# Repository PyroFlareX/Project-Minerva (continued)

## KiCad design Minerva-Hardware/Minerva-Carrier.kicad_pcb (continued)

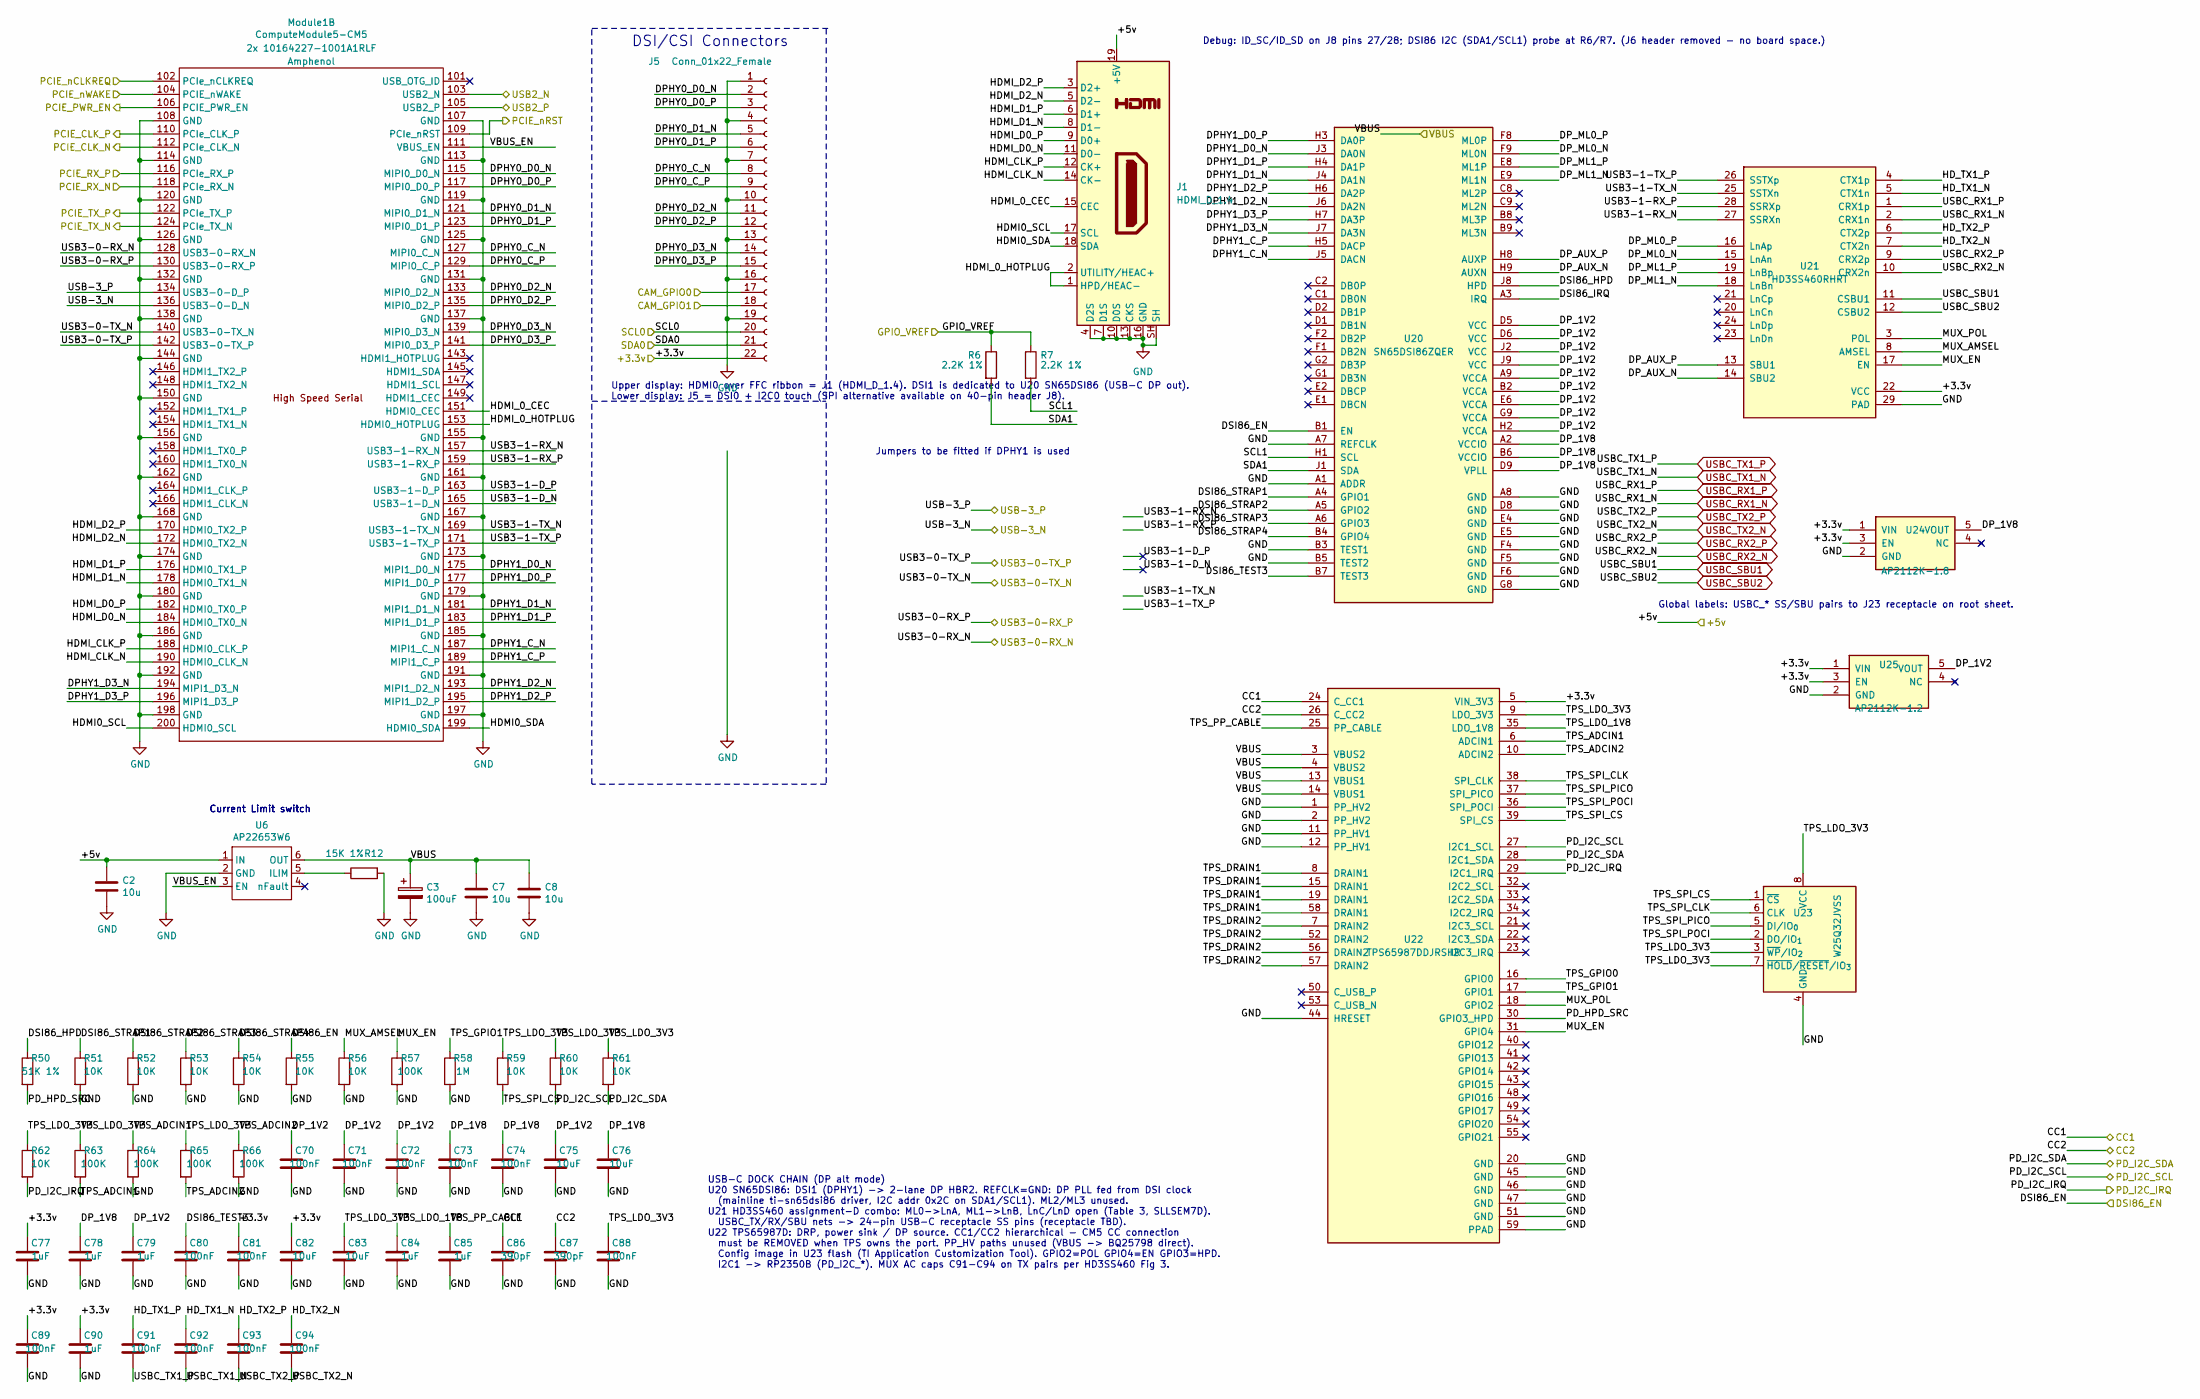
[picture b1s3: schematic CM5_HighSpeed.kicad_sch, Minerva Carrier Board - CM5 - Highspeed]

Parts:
C2, C7, C8: 10u; C_0805_2012Metric; Part Description 10uF 10% 10V Ceramic Capacitor X7R 0805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
C3: 100uF; CP_EIA-7343-31_Kemet-D; Part Description Capacitor, SP-Cap, 100u, 6.3V, 15mR ESR
C70, C71, C72, C73, C74, C80, C81, C88, C89, C91, C92, C93, C94: 100nF; C_0402_1005Metric; MPN EMK105B7104KV-F
C75, C76, C82, C83: 10uF; C_0603_1608Metric; MPN CL10A106KP8NNNC
C77, C78, C79, C84, C85, C90: 1uF; C_0402_1005Metric; MPN CC0402KRX5R6BB105
C86, C87: 390pF; C_0402_1005Metric; MPN GRM1555C1H391JA01D
J1: HDMI_D_1.4; TE_2-1734839-0_1x20-1MP_P0.5mm_Horizontal; MPN 2-1734839-0
J5: Conn_01x22_Female; Hirose_FH12-22S-0.5SH_1x22-1MP_P0.50mm_Horizontal; Part Description 22 Position FFC, FPC Connector Contacts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
Module1: ComputeModule5-CM5; Raspberry-Pi-5-Compute-Module; Part Description 100 Position Connector Receptacle, Cent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
R6, R7: 2.2K 1%; R_0402_1005Metric; Part Description Resistor 2.2K M1005 1% 63mW
R12: 15K 1%; R_0402_1005Metric; Part Description Resistor 15K M1005 1% 63mW
R50: 51K 1%; R_0402_1005Metric; MPN RC0402FR-0751KL
R51, R52, R53, R54, R55, R56, R59, R60, R61, R62: 10K; R_0402_1005Metric; MPN RC0402FR-0710KL
R57, R63, R64, R65, R66: 100K; R_0402_1005Metric; MPN RC0402FR-07100KL
R58: 1M; R_0402_1005Metric; MPN RC0402FR-071ML
U6: AP22653W6; SOT-23-6; Part Description Power Switch/Driver 1:1 P-Channel 2.1A 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
U20: SN65DSI86ZQER; nFBGA-64_ZQE_5x5mm_P0.5mm; Part Description MIPI DSI to DP1.2 bridge, LCSC C575556
U21: HD3SS460RHRT; WQFN-28-1EP_3.5x5.5mm_P0.5mm_EP2.05x4.05mm_ThermalVias; Part Description USB3/DP alt-mode passive mux, LCSC C215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
U22: TPS65987DDJRSHR; TPS65987D_VQFN56_RSH; Part Description USB-C PD3.0 controller w/ DP alt mode, 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
U23: W25Q32JVSS; SOIC-8_5.3x5.3mm_P1.27mm; Part Description TPS65987D config flash (any 2Mbit+ SPI 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
U24: AP2112K-1.8; SOT-23-5; Part Description 1.8V LDO for SN65DSI86 VCCIO/VPLL
U25: AP2112K-1.2; SOT-23-5; Part Description 1.2V LDO for SN65DSI86 VCC/VCCA

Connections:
+3.3v: C77.1, C81.1, C82.1, C89.1, C90.1, J5.22, U21.22 (VCC), U22.5 (VIN_3V3), U24.1 (VIN), U24.3 (EN), U25.1 (VIN), U25.3 (EN); also elsewhere on the board
/+5v: C2.1, J1.19 (+5V), U6.1 (IN); also elsewhere on the board
/CC1: C86.1, U22.24 (C_CC1); also elsewhere on the board
/CC2: C87.1, U22.26 (C_CC2); also elsewhere on the board
/CM5_GPIO/CAM_GPIO0: J5.17; also elsewhere on the board
/CM5_GPIO/CAM_GPIO1: J5.18; also elsewhere on the board
/CM5_GPIO/GPIO_VREF: R6.1, R7.1; also elsewhere on the board
/CM5_HighSpeed/DPHY0_C_N: J5.8, Module1.127 (MIPI0_C_N)
/CM5_HighSpeed/DPHY0_C_P: J5.9, Module1.129 (MIPI0_C_P)
/CM5_HighSpeed/DPHY0_D0_N: J5.2, Module1.115 (MIPI0_D0_N)
/CM5_HighSpeed/DPHY0_D0_P: J5.3, Module1.117 (MIPI0_D0_P)
/CM5_HighSpeed/DPHY0_D1_N: J5.5, Module1.121 (MIPI0_D1_N)
/CM5_HighSpeed/DPHY0_D1_P: J5.6, Module1.123 (MIPI0_D1_P)
/CM5_HighSpeed/DPHY0_D2_N: J5.11, Module1.133 (MIPI0_D2_N)
/CM5_HighSpeed/DPHY0_D2_P: J5.12, Module1.135 (MIPI0_D2_P)
/CM5_HighSpeed/DPHY0_D3_N: J5.14, Module1.139 (MIPI0_D3_N)
/CM5_HighSpeed/DPHY0_D3_P: J5.15, Module1.141 (MIPI0_D3_P)
/CM5_HighSpeed/DPHY1_C_N: Module1.187 (MIPI1_C_N), U20.J5 (DACN)
/CM5_HighSpeed/DPHY1_C_P: Module1.189 (MIPI1_C_P), U20.H5 (DACP)
/CM5_HighSpeed/DPHY1_D0_N: Module1.175 (MIPI1_D0_N), U20.J3 (DA0N)
/CM5_HighSpeed/DPHY1_D0_P: Module1.177 (MIPI1_D0_P), U20.H3 (DA0P)
/CM5_HighSpeed/DPHY1_D1_N: Module1.181 (MIPI1_D1_N), U20.J4 (DA1N)
/CM5_HighSpeed/DPHY1_D1_P: Module1.183 (MIPI1_D1_P), U20.H4 (DA1P)
/CM5_HighSpeed/DPHY1_D2_N: Module1.193 (MIPI1_D2_N), U20.J6 (DA2N)
/CM5_HighSpeed/DPHY1_D2_P: Module1.195 (MIPI1_D2_P), U20.H6 (DA2P)
/CM5_HighSpeed/DPHY1_D3_N: Module1.194 (MIPI1_D3_N), U20.J7 (DA3N)
/CM5_HighSpeed/DPHY1_D3_P: Module1.196 (MIPI1_D3_P), U20.H7 (DA3P)
/CM5_HighSpeed/DP_1V2: C70.1, C71.1, C72.1, C75.1, C79.1, U20.A9 (VCCA), U20.B2 (VCCA), U20.D5 (VCC), U20.D6 (VCC), U20.E6 (VCCA), U20.G9 (VCCA), U20.H2 (VCCA), U20.J2 (VCC), U20.J9 (VCC), U25.5 (VOUT)
/CM5_HighSpeed/DP_1V8: C73.1, C74.1, C76.1, C78.1, U20.A2 (VCCIO), U20.B6 (VCCIO), U20.D9 (VPLL), U24.5 (VOUT)
/CM5_HighSpeed/DP_AUX_N: U20.H9 (AUXN), U21.14 (SBU2)
/CM5_HighSpeed/DP_AUX_P: U20.H8 (AUXP), U21.13 (SBU1)
/CM5_HighSpeed/DP_ML0_N: U20.F9 (ML0N), U21.15 (LnAn)
/CM5_HighSpeed/DP_ML0_P: U20.F8 (ML0P), U21.16 (LnAp)
/CM5_HighSpeed/DP_ML1_N: U20.E9 (ML1N), U21.18 (LnBn)
/CM5_HighSpeed/DP_ML1_P: U20.E8 (ML1P), U21.19 (LnBp)
/CM5_HighSpeed/DSI86_HPD: R50.1, U20.J8 (HPD)
/CM5_HighSpeed/DSI86_IRQ: U20.A3 (IRQ)
/CM5_HighSpeed/DSI86_STRAP1: R51.1, U20.A4 (GPIO1)
/CM5_HighSpeed/DSI86_STRAP2: R52.1, U20.A5 (GPIO2)
/CM5_HighSpeed/DSI86_STRAP3: R53.1, U20.A6 (GPIO3)
/CM5_HighSpeed/DSI86_STRAP4: R54.1, U20.B4 (GPIO4)
/CM5_HighSpeed/DSI86_TEST3: C80.1, U20.B7 (TEST3)
/CM5_HighSpeed/HDMI0_SCL: J1.17 (SCL), Module1.200 (HDMI0_SCL)
/CM5_HighSpeed/HDMI0_SDA: J1.18 (SDA), Module1.199 (HDMI0_SDA)
/CM5_HighSpeed/HDMI_0_CEC: J1.15 (CEC), Module1.151 (HDMI0_CEC)
/CM5_HighSpeed/HDMI_0_HOTPLUG: J1.1 (HPD/HEAC-), J1.2 (UTILITY/HEAC+), Module1.153 (HDMI0_HOTPLUG)
/CM5_HighSpeed/HDMI_CLK_N: J1.14 (CK-), Module1.190 (HDMI0_CLK_N)
/CM5_HighSpeed/HDMI_CLK_P: J1.12 (CK+), Module1.188 (HDMI0_CLK_P)
/CM5_HighSpeed/HDMI_D0_N: J1.11 (D0-), Module1.184 (HDMI0_TX0_N)
/CM5_HighSpeed/HDMI_D0_P: J1.9 (D0+), Module1.182 (HDMI0_TX0_P)
/CM5_HighSpeed/HDMI_D1_N: J1.8 (D1-), Module1.178 (HDMI0_TX1_N)
/CM5_HighSpeed/HDMI_D1_P: J1.6 (D1+), Module1.176 (HDMI0_TX1_P)
/CM5_HighSpeed/HDMI_D2_N: J1.5 (D2-), Module1.172 (HDMI0_TX2_N)
/CM5_HighSpeed/HDMI_D2_P: J1.3 (D2+), Module1.170 (HDMI0_TX2_P)
/CM5_HighSpeed/HD_TX1_N: C92.1, U21.5 (CTX1n)
/CM5_HighSpeed/HD_TX1_P: C91.1, U21.4 (CTX1p)
/CM5_HighSpeed/HD_TX2_N: C94.1, U21.7 (CTX2n)
/CM5_HighSpeed/HD_TX2_P: C93.1, U21.6 (CTX2p)
/CM5_HighSpeed/MUX_AMSEL: R56.1, U21.8 (AMSEL)
/CM5_HighSpeed/MUX_EN: R57.1, U21.17 (EN), U22.31 (GPIO4)
/CM5_HighSpeed/MUX_POL: U21.3 (POL), U22.18 (GPIO2)
/CM5_HighSpeed/PCIE_CLK_N: Module1.112 (PCIe_CLK_N); also elsewhere on the board
/CM5_HighSpeed/PCIE_CLK_P: Module1.110 (PCIe_CLK_P); also elsewhere on the board
/CM5_HighSpeed/PCIE_PWR_EN: Module1.106 (PCIE_PWR_EN); also elsewhere on the board
/CM5_HighSpeed/PCIE_RX_N: Module1.118 (PCIe_RX_N); also elsewhere on the board
/CM5_HighSpeed/PCIE_RX_P: Module1.116 (PCIe_RX_P); also elsewhere on the board
/CM5_HighSpeed/PCIE_TX_N: Module1.124 (PCIe_TX_N); also elsewhere on the board
/CM5_HighSpeed/PCIE_TX_P: Module1.122 (PCIe_TX_P); also elsewhere on the board
/CM5_HighSpeed/PCIE_nCLKREQ: Module1.102 (PCIe_nCLKREQ); also elsewhere on the board
/CM5_HighSpeed/PCIE_nWAKE: Module1.104 (PCIE_nWAKE); also elsewhere on the board
/CM5_HighSpeed/PD_HPD_SRC: R50.2, U22.30 (GPIO3_HPD)
/CM5_HighSpeed/SCL0: J5.20; also elsewhere on the board
/CM5_HighSpeed/SCL1: R7.2, U20.H1 (SCL)
/CM5_HighSpeed/SDA0: J5.21; also elsewhere on the board
/CM5_HighSpeed/SDA1: R6.2, U20.J1 (SDA)
/CM5_HighSpeed/TPS_ADCIN1: R63.2, R64.1, U22.6 (ADCIN1)
/CM5_HighSpeed/TPS_ADCIN2: R65.2, R66.1, U22.10 (ADCIN2)
/CM5_HighSpeed/TPS_DRAIN1: U22.8 (DRAIN1), U22.15 (DRAIN1), U22.19 (DRAIN1), U22.58 (DRAIN1)
/CM5_HighSpeed/TPS_DRAIN2: U22.7 (DRAIN2), U22.52 (DRAIN2), U22.56 (DRAIN2), U22.57 (DRAIN2)
/CM5_HighSpeed/TPS_GPIO0: U22.16 (GPIO0)
/CM5_HighSpeed/TPS_GPIO1: R58.1, U22.17 (GPIO1)
/CM5_HighSpeed/TPS_LDO_1V8: C84.1, U22.35 (LDO_1V8)
/CM5_HighSpeed/TPS_LDO_3V3: C83.1, C88.1, R59.1, R60.1, R61.1, R62.1, R63.1, R65.1, U22.9 (LDO_3V3), U23.3 (~WP/IO_{2}), U23.7 (~HOLD/~RESET/IO_{3}), U23.8 (VCC)
/CM5_HighSpeed/TPS_PP_CABLE: C85.1, U22.25 (PP_CABLE)
/CM5_HighSpeed/TPS_SPI_CLK: U22.38 (SPI_CLK), U23.6 (CLK)
/CM5_HighSpeed/TPS_SPI_CS: R59.2, U22.39 (SPI_CS), U23.1 (~CS)
/CM5_HighSpeed/TPS_SPI_PICO: U22.37 (SPI_PICO), U23.5 (DI/IO_{0})
/CM5_HighSpeed/TPS_SPI_POCI: U22.36 (SPI_POCI), U23.2 (DO/IO_{1})
/CM5_HighSpeed/USB3-0-RX_N: Module1.128 (USB3-0-RX_N); also elsewhere on the board
/CM5_HighSpeed/USB3-0-RX_P: Module1.130 (USB3-0-RX_P); also elsewhere on the board
/CM5_HighSpeed/USB3-0-TX_N: Module1.140 (USB3-0-TX_N); also elsewhere on the board
/CM5_HighSpeed/USB3-0-TX_P: Module1.142 (USB3-0-TX_P); also elsewhere on the board
/CM5_HighSpeed/USB3-1-D_N: Module1.165 (USB3-1-D_N)
/CM5_HighSpeed/USB3-1-D_P: Module1.163 (USB3-1-D_P)
/CM5_HighSpeed/USB3-1-RX_N: Module1.157 (USB3-1-RX_N), U21.27 (SSRXn)
/CM5_HighSpeed/USB3-1-RX_P: Module1.159 (USB3-1-RX_P), U21.28 (SSRXp)
/CM5_HighSpeed/USB3-1-TX_N: Module1.169 (USB3-1-TX_N), U21.25 (SSTXn)
/CM5_HighSpeed/USB3-1-TX_P: Module1.171 (USB3-1-TX_P), U21.26 (SSTXp)
/CM5_HighSpeed/USB-3_N: Module1.136 (USB3-0-D_N); also elsewhere on the board
/CM5_HighSpeed/USB-3_P: Module1.134 (USB3-0-D_P); also elsewhere on the board
/CM5_HighSpeed/VBUS_EN: Module1.111 (VBUS_EN), U6.3 (EN)
/DSI86_EN: R55.1, U20.B1 (EN); also elsewhere on the board
/PCIE_nRST: Module1.109 (PCIe_nRST); also elsewhere on the board
/PD_I2C_IRQ: R62.2, U22.29 (I2C1_IRQ); also elsewhere on the board
/PD_I2C_SCL: R60.2, U22.27 (I2C1_SCL); also elsewhere on the board
/PD_I2C_SDA: R61.2, U22.28 (I2C1_SDA); also elsewhere on the board
/USB2_N: Module1.103 (USB2_N); also elsewhere on the board
/USB2_P: Module1.105 (USB2_P); also elsewhere on the board
/VBUS: C3.1, C7.1, C8.1, U6.6 (OUT), U22.3 (VBUS2), U22.4 (VBUS2), U22.13 (VBUS1), U22.14 (VBUS1); also elsewhere on the board
GND: C2.2, C3.2, C7.2, C8.2, C70.2, C71.2, C72.2, C73.2, C74.2, C75.2, C76.2, C77.2, C78.2, C79.2, C80.2, C81.2, C82.2, C83.2, C84.2, C85.2, C86.2, C87.2, C88.2, C89.2, C90.2, J1.4 (D2S), J1.7 (D1S), J1.10 (D0S), J1.13 (CKS), J1.16 (GND), J1.20, J1.MP, J1.SH, J5.1, J5.4, J5.7, J5.10, J5.13, J5.16, J5.19, Module1.107 (GND), Module1.108 (GND), Module1.113 (GND), Module1.114 (GND), Module1.119 (GND), Module1.120 (GND), Module1.125 (GND), Module1.126 (GND), Module1.131 (GND), Module1.132 (GND), Module1.137 (GND), Module1.138 (GND), Module1.144 (GND), Module1.150 (GND), Module1.155 (GND), Module1.156 (GND), Module1.161 (GND), Module1.162 (GND), Module1.167 (GND), Module1.168 (GND), Module1.173 (GND), Module1.174 (GND), Module1.179 (GND), Module1.180 (GND), Module1.185 (GND), Module1.186 (GND), Module1.191 (GND), Module1.192 (GND), Module1.197 (GND), Module1.198 (GND), R12.2, R51.2, R52.2, R53.2, R54.2, R55.2, R56.2, R57.2, R58.2, R64.2, R66.2, U6.2 (GND), U20.A1 (ADDR), U20.A7 (REFCLK), U20.A8 (GND), U20.B3 (TEST1), U20.B5 (TEST2), U20.D8 (GND), U20.E4 (GND), U20.E5 (GND), U20.F4 (GND), U20.F5 (GND), U20.F6 (GND), U20.G8 (GND), U21.29 (PAD), U22.1 (PP_HV2), U22.2 (PP_HV2), U22.11 (PP_HV1), U22.12 (PP_HV1), U22.20 (GND), U22.44 (HRESET), U22.45 (GND), U22.46 (GND), U22.47 (GND), U22.51 (GND), U22.59 (PPAD), U23.4 (GND), U24.2 (GND), U25.2 (GND); also elsewhere on the board
unnamed: R12.1, U6.5 (ILIM)
USBC_RX1_N: U21.2 (CRX1n); also elsewhere on the board
USBC_RX1_P: U21.1 (CRX1p); also elsewhere on the board
USBC_RX2_N: U21.10 (CRX2n); also elsewhere on the board
USBC_RX2_P: U21.9 (CRX2p); also elsewhere on the board
USBC_SBU1: U21.11 (CSBU1); also elsewhere on the board
USBC_SBU2: U21.12 (CSBU2); also elsewhere on the board
USBC_TX1_N: C92.2; also elsewhere on the board
USBC_TX1_P: C91.2; also elsewhere on the board
USBC_TX2_N: C94.2; also elsewhere on the board
USBC_TX2_P: C93.2; also elsewhere on the board

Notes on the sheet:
Upper display: HDMI0 over FFC ribbon = J1 (HDMI_D_1.4). DSI1 is dedicated to U20 SN65DSI86 (USB-C DP out). Lower display: J5 = DSI0 + I2C0 touch (SPI alternative available on 40-pin header J8).
Jumpers to be fitted if DPHY1 is used
Current Limit switch
Global labels: USBC_* SS/SBU pairs to J23 receptacle on root sheet.
DSI/CSI Connectors
USB-C DOCK CHAIN (DP alt mode) U20 SN65DSI86: DSI1 (DPHY1) -> 2-lane DP HBR2. REFCLK=GND: DP PLL fed from DSI clock (mainline ti-sn65dsi86 driver, I2C addr 0x2C on SDA1/SCL1). ML2/ML3 unused. U21 HD3SS460 assignment-D combo: ML0->LnA, ML1->LnB, LnC/LnD open (Table 3, SLLSEM7D). USBC_TX/RX/SBU nets 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
Debug: ID_SC/ID_SD on J8 pins 27/28; DSI86 I2C (SDA1/SCL1) probe at R6/R7. (J6 header removed - no board space.)

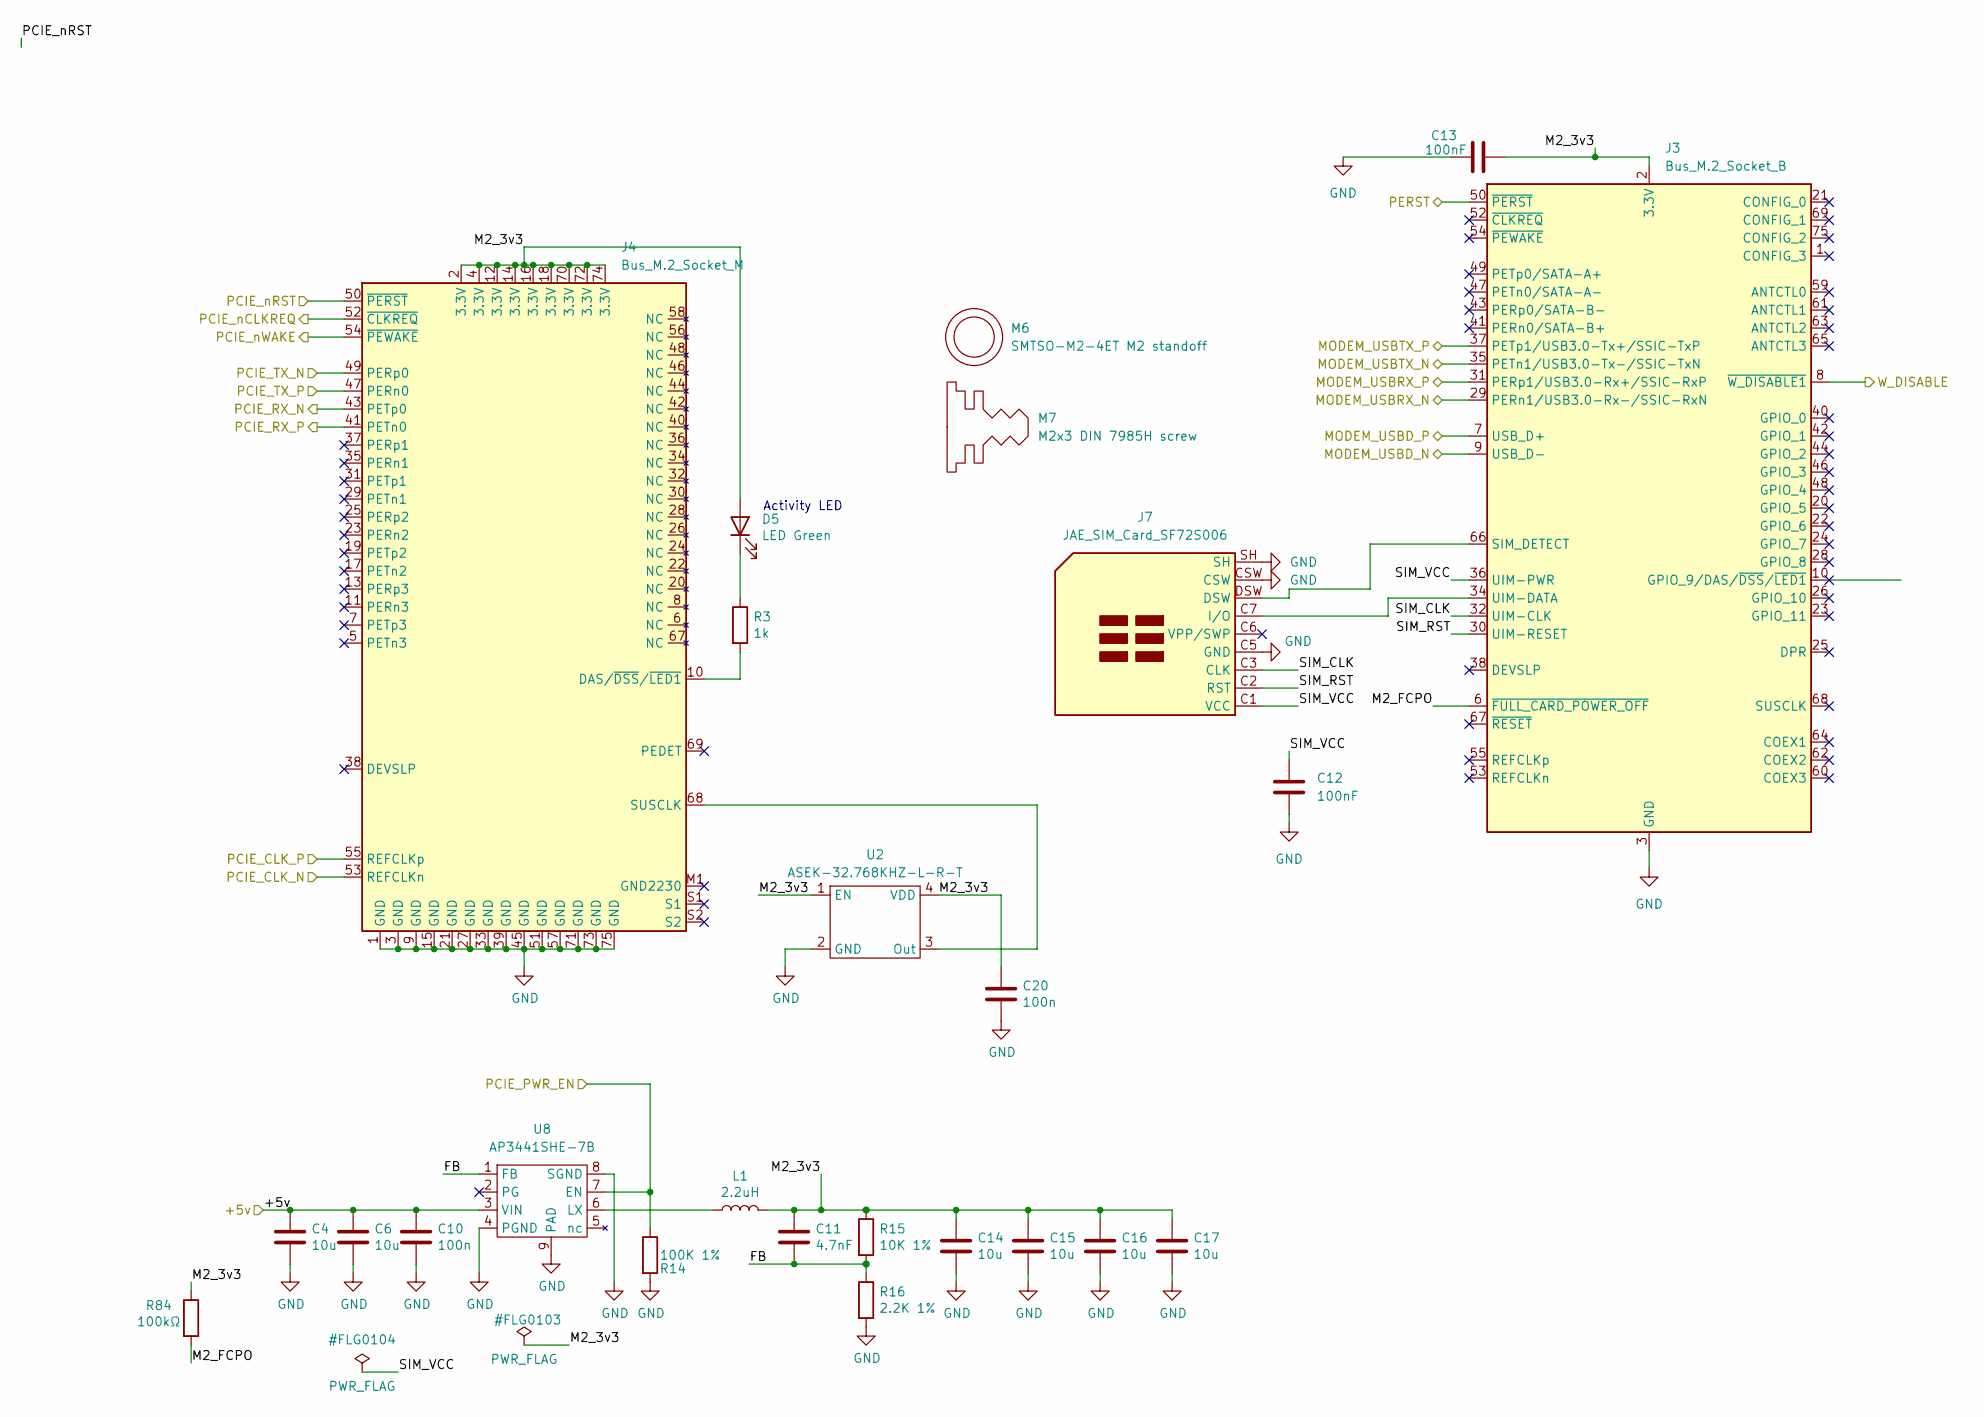
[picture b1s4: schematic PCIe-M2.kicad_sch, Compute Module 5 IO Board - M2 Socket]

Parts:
C4, C6, C14, C15, C16, C17: 10u; C_0805_2012Metric; Part Description 10uF 10% 10V Ceramic Capacitor X7R 0805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
C10, C20: 100n; C_0402_1005Metric; Part Description 0.1uF 10% 16V Ceramic Capacitor X7R 040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
C11: 4.7nF; C_0402_1005Metric; Part Description 4.7nF capacitor 0402
C12, C13: 100nF; C_0402_1005Metric; MPN EMK105B7104KV-F
D5: LED Green; LED_0603_1608Metric; Part Description Green 572nm LED Indication - Discrete 2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
J3: Bus_M.2_Socket_B; CONN67_2199230_TEC; MPN 1-2199230-3
J4: Bus_M.2_Socket_M; M.2 M Key socket 2230; MPN 1-2199230-6
J7: JAE_SIM_Card_SF72S006; MPN SF72S006VBDR2500
L1: 2.2uH; L_Bourns_SRP5030T; Part Description Inductor, SMT, 2520, 2u2, IRMS=7A, ISAT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
M6: SMTSO-M2-4ET M2 standoff; SMTSO-M2-4ET; Part Description Solder nut for M.2 slot
M7: M2x3 DIN 7985H screw; Part Description M.2 Screw
R3: 1k; R_0402_1005Metric; Part Description Resistor 1K M1005 1% 63mW
R14: 100K 1%; R_0402_1005Metric; Part Description Resistor 100K M1005 1% 63mW
R15: 10K 1%; R_0402_1005Metric; Part Description Resistor 10K M1005 1% 63mW
R16: 2.2K 1%; R_0402_1005Metric; Part Description Resistor 2.2K M1005 1% 63mW
R84: 100kΩ; R_0402_1005Metric; MPN RC0402FR-07100KL
U2: ASEK-32.768KHZ-L-R-T; Crystal_SMD_3225-4Pin_3.2x2.5mm; Part Description 32KHz Xtal oscilator
U8: AP3441SHE-7B; DFN-8-1EP_2x2mm_P0.5mm_EP1.05x1.75mm; Part Description 3A DC-DC converter

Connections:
/+5v: C4.1, C6.1, C10.1, U8.3 (VIN); also elsewhere on the board
/CM5_HighSpeed/PCIE_CLK_N: J4.53 (REFCLKn); also elsewhere on the board
/CM5_HighSpeed/PCIE_CLK_P: J4.55 (REFCLKp); also elsewhere on the board
/CM5_HighSpeed/PCIE_PWR_EN: R14.1, U8.7 (EN); also elsewhere on the board
/CM5_HighSpeed/PCIE_RX_N: J4.43 (PETp0); also elsewhere on the board
/CM5_HighSpeed/PCIE_RX_P: J4.41 (PETn0); also elsewhere on the board
/CM5_HighSpeed/PCIE_TX_N: J4.49 (PERp0); also elsewhere on the board
/CM5_HighSpeed/PCIE_TX_P: J4.47 (PERn0); also elsewhere on the board
/CM5_HighSpeed/PCIE_nCLKREQ: J4.52 (~CLKREQ); also elsewhere on the board
/CM5_HighSpeed/PCIE_nWAKE: J4.54 (~PEWAKE); also elsewhere on the board
/CM5_HighSpeed/USB3-0-RX_N: J3.29 (PERn1/USB3.0-Rx-/SSIC-RxN); also elsewhere on the board
/CM5_HighSpeed/USB3-0-RX_P: J3.31 (PERp1/USB3.0-Rx+/SSIC-RxP); also elsewhere on the board
/CM5_HighSpeed/USB3-0-TX_N: J3.35 (PETn1/USB3.0-Tx-/SSIC-TxN); also elsewhere on the board
/CM5_HighSpeed/USB3-0-TX_P: J3.37 (PETp1/USB3.0-Tx+/SSIC-TxP); also elsewhere on the board
/CM5_HighSpeed/USB-3_N: J3.9 (USB_D-); also elsewhere on the board
/CM5_HighSpeed/USB-3_P: J3.7 (USB_D+); also elsewhere on the board
/PCIE_nRST: J3.50 (~PERST), J4.50 (~PERST); also elsewhere on the board
/PCIe-M2/FB: C11.2, R15.2, R16.1, U8.1 (FB)
/PCIe-M2/M2_3v3: C11.1, C13.2, C14.1, C15.1, C16.1, C17.1, C20.1, D5.2 (A), J3.2 (3.3V), J3.4 (3.3V), J3.70 (3.3V), J3.72 (3.3V), J3.74 (3.3V), J4.2 (3.3V), J4.4 (3.3V), J4.12 (3.3V), J4.14 (3.3V), J4.16 (3.3V), J4.18 (3.3V), J4.70 (3.3V), J4.72 (3.3V), J4.74 (3.3V), L1.2, R15.1, R84.1, U2.1 (EN), U2.4 (VDD)
/PCIe-M2/M2_FCPO: J3.6 (~FULL_CARD_POWER_OFF), R84.2
/PCIe-M2/SIM_CLK: J3.32 (UIM-CLK), J7.C3 (CLK)
/PCIe-M2/SIM_RST: J3.30 (UIM-RESET), J7.C2 (RST)
/PCIe-M2/SIM_VCC: C12.1, J3.36 (UIM-PWR), J7.C1 (VCC)
/PCIe-M2/W_DISABLE: J3.8 (~W_DISABLE1)
GND: C4.2, C6.2, C10.2, C12.2, C13.1, C14.2, C15.2, C16.2, C17.2, C20.2, J3.3 (GND), J3.5 (GND), J3.11 (GND), J3.27 (GND), J3.33 (GND), J3.39 (GND), J3.45 (GND), J3.51 (GND), J3.57 (GND), J3.71 (GND), J3.73 (GND), J3.76, J3.77, J4.1 (GND), J4.3 (GND), J4.9 (GND), J4.15 (GND), J4.21 (GND), J4.27 (GND), J4.33 (GND), J4.39 (GND), J4.45 (GND), J4.51 (GND), J4.57 (GND), J4.71 (GND), J4.73 (GND), J4.75 (GND), J4.M1 (GND2230), J7.C5 (GND), J7.CSW, J7.SH, M6.1, R14.2, R16.2, U2.2 (GND), U8.4 (PGND), U8.8 (SGND), U8.9 (PAD); also elsewhere on the board
unnamed: D5.1 (K), R3.1
unnamed: J3.66 (SIM_DETECT), J7.DSW
unnamed: J3.34 (UIM-DATA), J7.C7 (I/O)
unnamed: J4.10 (DAS/~DSS/~LED1), R3.2
unnamed: J4.68 (SUSCLK), U2.3 (Out)
unnamed: L1.1, U8.6 (LX)

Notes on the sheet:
Activity LED

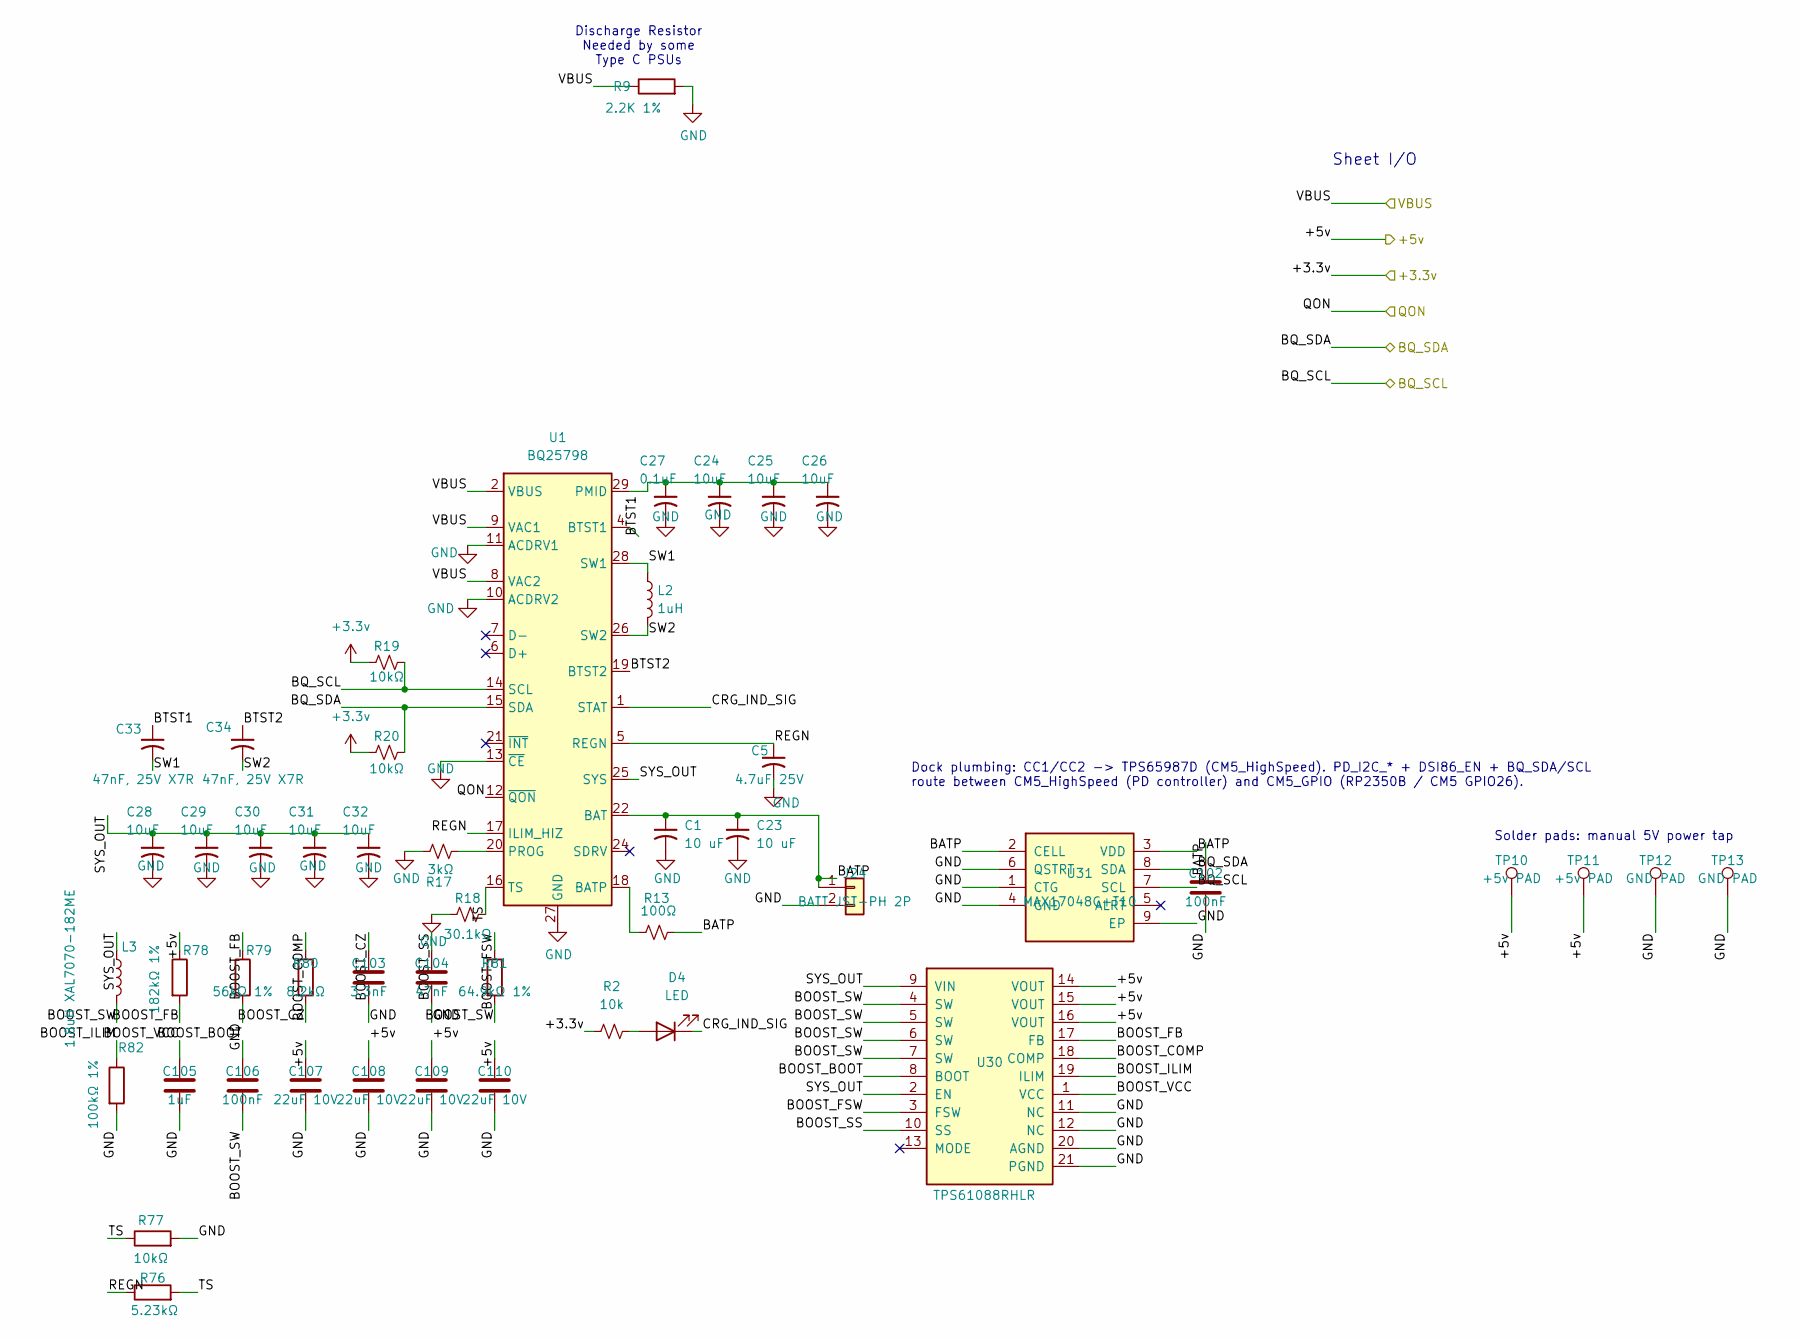
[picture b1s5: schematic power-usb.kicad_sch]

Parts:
C1, C23: 10 uF; C_0603_1608Metric; MPN CL10A106KP8NNNC
C5: 4.7uF 25V; C_0603_1608Metric; MPN GRM188R61E475KE11D
C24, C25, C26: 10uF; C_0805_2012Metric; MPN GRM21BR61E106KA73L
C27: 0.1uF; C_0402_1005Metric; MPN GRM155R71H104KE14D
C28, C29, C30, C31, C32: 10uF; C_0603_1608Metric; MPN CL10A106KP8NNNC
C33, C34: 47nF, 25V X7R; C_0402_1005Metric; MPN GRM155R71E473KA88D
C102, C106: 100nF; C_0402_1005Metric; MPN EMK105B7104KV-F
C103: 3.3nF; C_0402_1005Metric; MPN GRM1555C1H332JE01D
C104: 47nF; C_0402_1005Metric; MPN GRM155R71E473KA88D
C105: 1uF; C_0402_1005Metric; MPN CC0402KRX5R6BB105
C107, C108, C109, C110: 22uF 10V; C_0805_2012Metric; MPN GRM21BR61A226ME44L
D4: LED; LED_0402_1005Metric; MPN SML-P12UTT86R
J24: BATT JST-PH 2P; JST_PH_B2B-PH-K_1x02_P2.00mm_Vertical; MPN B2B-PH-K-S(LF)(SN)
L2: 1uH; L_Bourns_SRP5030T; MPN SRP5030T-1R0M
L3: 1.8uH XAL7070-182ME; L_Coilcraft_XAL7070-XXX; MPN XAL7070-182MEC
R2: 10k; R_0402_1005Metric; MPN RC0402FR-0710KL
R9: 2.2K 1%; R_0402_1005Metric; Part Description Resistor 2.2K M1005 1% 63mW
R13: 100Ω; R_0402_1005Metric; MPN RC0402FR-07100RL
R17: 3kΩ; R_0402_1005Metric; MPN RC0402FR-073KL
R18: 30.1kΩ; R_0402_1005Metric; MPN RC0402FR-0730K1L
R19, R20, R77: 10kΩ; R_0402_1005Metric; MPN RC0402FR-0710KL
R76: 5.23kΩ; R_0402_1005Metric; MPN CRCW04025K23FKED
R78: 182kΩ 1%; R_0402_1005Metric; MPN RC0402FR-07182KL
R79: 56kΩ 1%; R_0402_1005Metric; MPN RC0402FR-0756KL
R80: 8.2kΩ; R_0402_1005Metric; MPN RT0402FRE078K2L
R81: 64.9kΩ 1%; R_0402_1005Metric; MPN CRCW040264K9FKED
R82: 100kΩ 1%; R_0402_1005Metric; MPN RC0402FR-07100KL
TP10, TP11: +5v PAD; TestPoint_Pad_D2.0mm; MPN N/A
TP12, TP13: GND PAD; TestPoint_Pad_D2.0mm; MPN N/A
U1: BQ25798; Texas_RQM0029A_VQFN-29_4x4mm_P0.4mm; MPN BQ25798RQMR
U30: TPS61088RHLR; VQFN-20-1EP_3.5x4.5mm_P0.5mm_EP2.15x3.15mm; MPN TPS61088RHLR
U31: MAX17048G+T10; MAX17048_TDFN8; MPN MAX17048G+T10

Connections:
+3.3v: R2.1, R19.1, R20.1; also elsewhere on the board
/+5v: C107.1, C108.1, C109.1, C110.1, R78.1, TP10.1, TP11.1, U30.14 (VOUT), U30.15 (VOUT), U30.16 (VOUT); also elsewhere on the board
/BQ_SCL: R19.2, U1.14 (SCL), U31.7 (SCL); also elsewhere on the board
/BQ_SDA: R20.2, U1.15 (SDA), U31.8 (SDA); also elsewhere on the board
/Power and UserIO/BATP: C1.1, C23.1, C102.1, J24.1, R13.2, U1.22 (BAT), U1.23 (BAT), U31.2 (CELL), U31.3 (VDD)
/Power and UserIO/BOOST_BOOT: C106.1, U30.8 (BOOT)
/Power and UserIO/BOOST_COMP: R80.1, U30.18 (COMP)
/Power and UserIO/BOOST_CZ: C103.1, R80.2
/Power and UserIO/BOOST_FB: R78.2, R79.1, U30.17 (FB)
/Power and UserIO/BOOST_FSW: R81.1, U30.3 (FSW)
/Power and UserIO/BOOST_ILIM: R82.1, U30.19 (ILIM)
/Power and UserIO/BOOST_SS: C104.1, U30.10 (SS)
/Power and UserIO/BOOST_SW: C106.2, L3.2, R81.2, U30.4 (SW), U30.5 (SW), U30.6 (SW), U30.7 (SW)
/Power and UserIO/BOOST_VCC: C105.1, U30.1 (VCC)
/Power and UserIO/BTST1: C33.1, U1.4 (BTST1)
/Power and UserIO/BTST2: C34.1, U1.19 (BTST2)
/Power and UserIO/CRG_IND_SIG: D4.1 (K), U1.1 (STAT)
/Power and UserIO/REGN: C5.1, R76.1, U1.5 (REGN), U1.17 (ILIM_HIZ)
/Power and UserIO/SW1: C33.2, L2.1, U1.28 (SW1)
/Power and UserIO/SW2: C34.2, L2.2, U1.26 (SW2)
/Power and UserIO/SYS_OUT: C28.1, C29.1, C30.1, C31.1, C32.1, L3.1, U1.25 (SYS), U30.2 (EN), U30.9 (VIN)
/Power and UserIO/TS: R18.2, R76.2, R77.1, U1.16 (TS)
/QON: U1.12 (~QON); also elsewhere on the board
/VBUS: R9.1, U1.2 (VBUS), U1.3 (VBUS), U1.8 (VAC2), U1.9 (VAC1); also elsewhere on the board
GND: C1.2, C5.2, C23.2, C24.2, C25.2, C26.2, C27.2, C28.2, C29.2, C30.2, C31.2, C32.2, C102.2, C103.2, C104.2, C105.2, C107.2, C108.2, C109.2, C110.2, J24.2, R9.2, R17.2, R18.1, R77.2, R79.2, R82.2, TP12.1, TP13.1, U1.10 (ACDRV2), U1.11 (ACDRV1), U1.13 (~CE), U1.27 (GND), U30.11 (NC), U30.12 (NC), U30.20 (AGND), U30.21 (PGND), U31.1 (CTG), U31.4 (GND), U31.6 (QSTRT), U31.9 (EP); also elsewhere on the board
unnamed: D4.2 (A), R2.2
unnamed: R13.1, U1.18 (BATP)
unnamed: C24.1, C25.1, C26.1, C27.1, U1.29 (PMID)
unnamed: R17.1, U1.20 (PROG)

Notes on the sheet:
Sheet I/O
Discharge Resistor Needed by some Type C PSUs
Solder pads: manual 5V power tap
Dock plumbing: CC1/CC2 -> TPS65987D (CM5_HighSpeed). PD_I2C_* + DSI86_EN + BQ_SDA/SCL route between CM5_HighSpeed (PD controller) and CM5_GPIO (RP2350B / CM5 GPIO26).
